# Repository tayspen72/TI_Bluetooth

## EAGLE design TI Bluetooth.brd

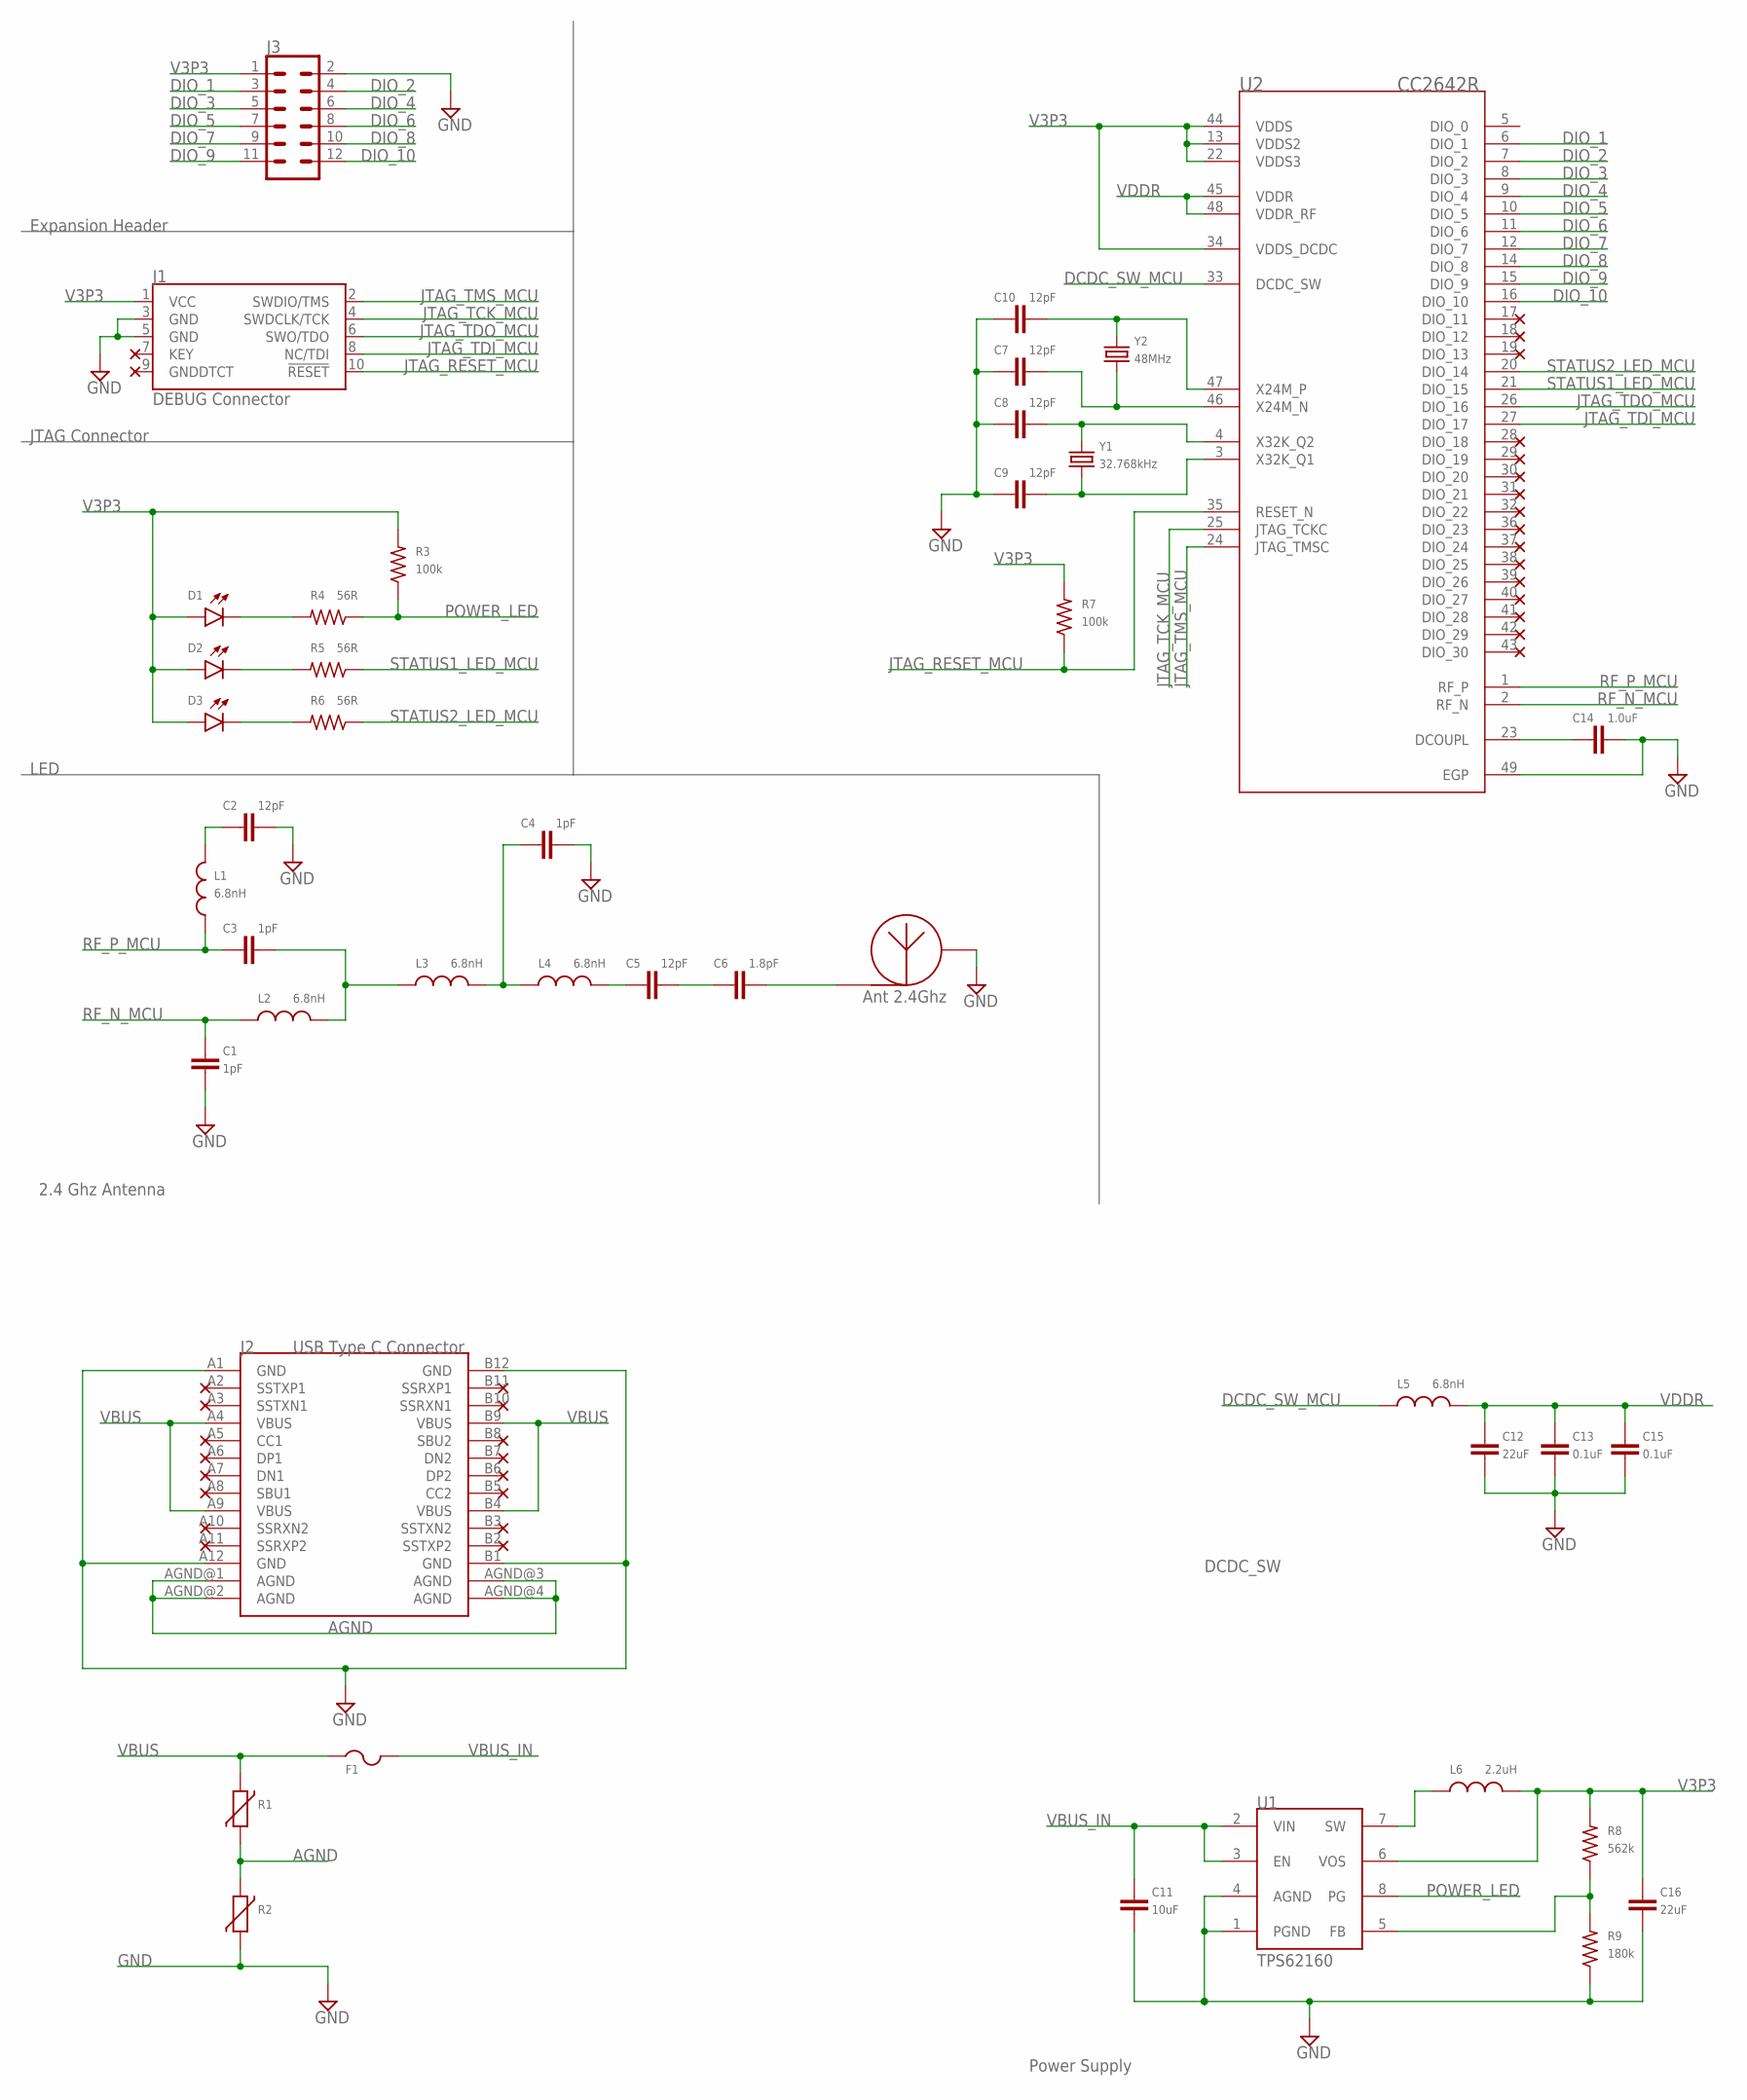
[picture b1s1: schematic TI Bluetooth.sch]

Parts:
ANT1: TI_AN043
C1, C3, C4: 1pF; C0603
C2, C5, C7, C8, C9, C10: 12pF; C0603
C6: 1.8pF; C0603
C11: 10uF; C0603
C12, C16: 22uF; C0603
C13, C15: 0.1uF; C0603
C14: 1.0uF; C0603
D1: POWER; LED-1206
D2: STATUS1; LED-1206
D3: STATUS2; LED-1206
F1: 1206L110THYR; R1206
J1: DEBUG Connector; SAMTECH_FTSH-105-01
J2: USB Type C Connector; USB-C31-S-RA-CS1-BK-TR
J3: Expansion Header; 2X6
L1, L2, L3, L4, L5: 6.8nH; INDC1608X95N
L6: 2.2uH; INDC1608X95N
R1, R2: V5.5MLA; CT/CN0603
R3, R7: 100k; R0603
R4, R5, R6: 56R; R0603
R8: 562k; R0603
R9: 180k; R0603
U1: TPS62160; SOP65P490X110-8N
U2: CC2642R; QFN50P700X690X100-49T515N
Y1: 32.768kHz; CRYSTAL-PTH-2X6-CYL
Y2: 48MHz; CRYSTAL-SMD-5X3.2-2PAD

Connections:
AGND: J2.AGND@1 (AGND), J2.AGND@2 (AGND), J2.AGND@3 (AGND), J2.AGND@4 (AGND), R1.2, R2.1
DCDC_SW_MCU: L5.1, U2.33 (DCDC_SW)
DIO_1: J3.3, U2.6 (DIO_1)
DIO_2: J3.4, U2.7 (DIO_2)
DIO_3: J3.5, U2.8 (DIO_3)
DIO_4: J3.6, U2.9 (DIO_4)
DIO_5: J3.7, U2.10 (DIO_5)
DIO_6: J3.8, U2.11 (DIO_6)
DIO_7: J3.9, U2.12 (DIO_7)
DIO_8: J3.10, U2.14 (DIO_8)
DIO_9: J3.11, U2.15 (DIO_9)
DIO_10: J3.12, U2.16 (DIO_10)
GND: ANT1.FEED, ANT1.RETURN, C1.2, C2.2, C4.2, C6.2, C7.1, C8.1, C9.1, C10.2, C11.2, C12.2, C13.2, C14.2, C15.2, C16.2, J1.3 (GND), J1.5 (GND), J2.A1 (GND), J2.A12 (GND), J2.B1 (GND), J2.B12 (GND), J3.2, R2.2, R9.1, U1.1 (PGND), U1.4 (AGND), U2.49 (EGP)
JTAG_RESET_MCU: J1.10 (!RESET), R7.1, U2.35 (RESET_N)
JTAG_TCK_MCU: J1.4 (SWDCLK/TCK), U2.25 (JTAG_TCKC)
JTAG_TDI_MCU: J1.8 (NC/TDI), U2.27 (DIO_17)
JTAG_TDO_MCU: J1.6 (SWO/TDO), U2.26 (DIO_16)
JTAG_TMS_MCU: J1.2 (SWDIO/TMS), U2.24 (JTAG_TMSC)
unnamed: C8.2, U2.4 (X32K_Q2), Y1.1
unnamed: C9.2, U2.3 (X32K_Q1), Y1.2
unnamed: C10.1, U2.47 (X24M_P), Y2.P$2 (2)
unnamed: C14.1, U2.23 (DCOUPL)
unnamed: C2.1, L1.2
unnamed: C7.2, U2.46 (X24M_N), Y2.P$1 (1)
unnamed: L6.1, U1.7 (SW)
unnamed: C4.1, L3.2, L4.1
unnamed: C3.2, L2.2, L3.1
unnamed: C5.1, L4.2
unnamed: R8.1, R9.2, U1.5 (FB)
unnamed: C5.2, C6.1
unnamed: D1.C, R4.2
unnamed: D3.C, R6.2
unnamed: D2.C, R5.2
POWER_LED: R3.1, R4.1, U1.8 (PG)
RF_N_MCU: C1.1, L2.1, U2.2 (RF_N)
RF_P_MCU: C3.1, L1.1, U2.1 (RF_P)
STATUS1_LED_MCU: R5.1, U2.21 (DIO_15)
STATUS2_LED_MCU: R6.1, U2.20 (DIO_14)
V3P3: C16.1, D1.A, D2.A, D3.A, J1.1 (VCC), J3.1, L6.2, R3.2, R7.2, R8.2, U1.6 (VOS), U2.13 (VDDS2), U2.22 (VDDS3), U2.34 (VDDS_DCDC), U2.44 (VDDS)
VBUS: F1.1, J2.A4 (VBUS), J2.A9 (VBUS), J2.B4 (VBUS), J2.B9 (VBUS), R1.1
VBUS_IN: C11.1, F1.2, U1.2 (VIN), U1.3 (EN)
VDDR: C12.1, C13.1, C15.1, L5.2, U2.45 (VDDR), U2.48 (VDDR_RF)

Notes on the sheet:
2.4 Ghz Antenna
JTAG Connector
DCDC_SW
Power Supply
Expansion Header
LED

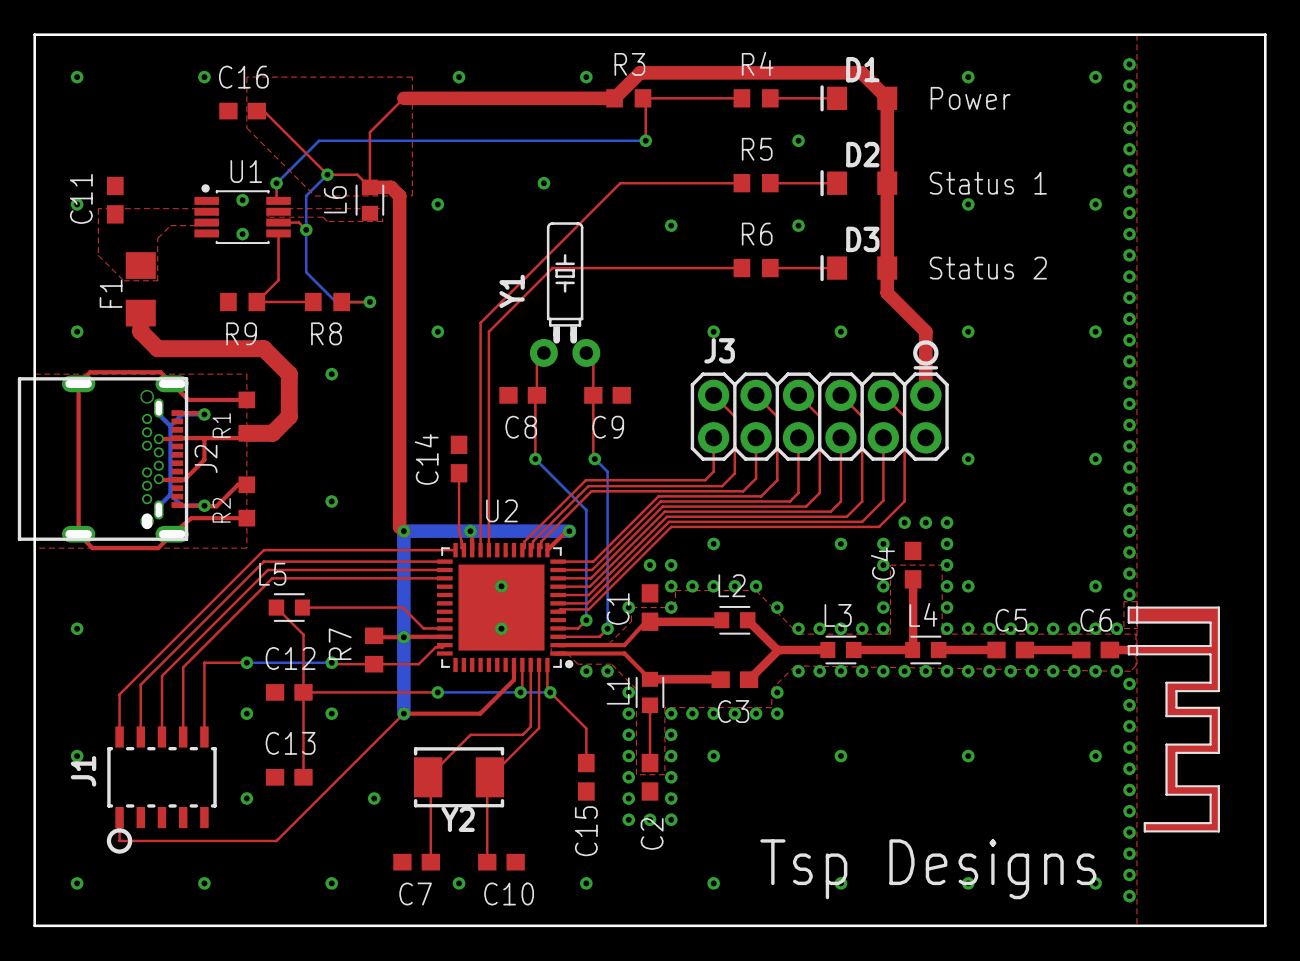
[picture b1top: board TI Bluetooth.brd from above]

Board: 2 copper layers, 73.2 x 52.9 mm, 43 parts (0 on the bottom side), 42 nets.

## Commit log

2020-11-12 Split to two frames
2020-11-12 Initial routing
2020-11-12 More initial routing
2020-11-13 Much of routing finished
2020-11-15 Shrunk board size
2020-11-26 Fixed PCB antenna and width of power traces
2020-12-09 Updates to silkscreen and power trace-width

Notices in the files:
parts and their libraries:
SparkFun-LED: Licensing: Creative Commons ShareAlike 4.0 International - https://creativecommons.org/licenses/by-sa/4.0
